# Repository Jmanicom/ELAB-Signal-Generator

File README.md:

# ELAB-Signal-Generator
A square wave generator with adjustable frequency, gain, and offset control. Designed as a part of UBC's ELAB PCB design course.

### **Skills used in this project**
***KiCad, Analog Circuit Design, Hand Soldering, Testing/Validation***

---

# Design
The design for this signal generator is not complex, this is because it's main purpose was to provide an opportunity to design 
and assemble a PCB from the start to finish of the production cycle. This included schematic capture, component/footprint library 
creation, component layout, laying traces, and laying polygon pours. In the second stage of the course, we received our boards and 
components and assembled them using hand soldering, and tested them using an oscilloscope to view our signals and test the various 
adjustments.

## Power Supply
The signal generator utilizes +/-5V rails to be able produce a maximum of a 10V peak-to-peak
signal. 15V  comes from a barrel jack connections from a wall adapter, which is then 
regulated using the **LM7805** to drop to it to +5V. This rail then feeds into the **MAX889** that
produces the complimentary -5V rail. Output capacitors are used to help with input noise, and output voltage ripple.

## Signal Amplifier
The square wave signal is generated by the **NE555**, that includes a frequency adjust potentiometer. This signal is then fed to 
the **AD8039** with two amplifier stages to control gain and offset respectively. Additional bypass capacitors are placed
on the op-amps power rails to help with further noise reduction and to help stabilize voltage. Finally, a 3.3V peak-limiter zener
diode is placed on the output which can be engaged with the use of a jumper. 

## PCB Design
With this being my first attempt at PCB design, there is room for improvement with my traces decisions component placement.
With this project, we were constrained on the size of board that we could use, additionally, I wanted to make a unique shape
for my board that tends to be a popular shape for small desings that need to be mounted.

The large 1206 capacitors were placed on the back side of the board as they are quite bulky and left very little room for other
components on the board. This board features 2-layers with ground pours on each layer, as well as stitching vias to help further
with noise.

# Assembly

# Testing

# Notes

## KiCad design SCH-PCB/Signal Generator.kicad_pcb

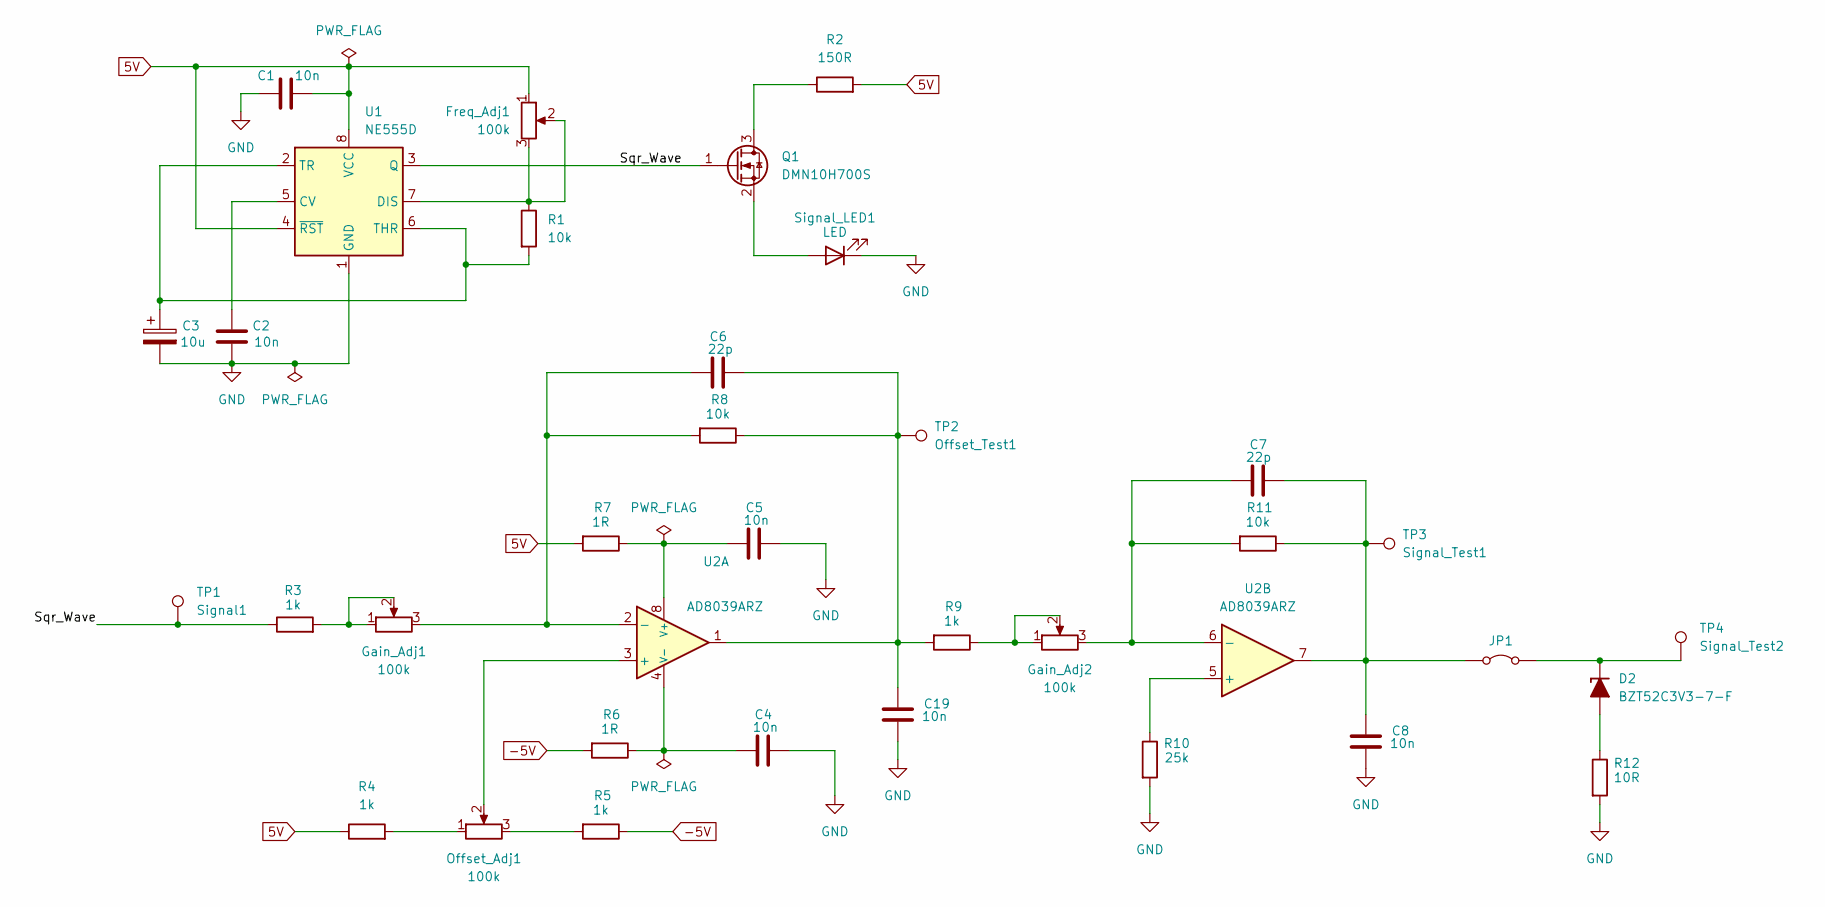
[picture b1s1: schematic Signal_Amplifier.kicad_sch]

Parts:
C1, C2, C4, C5, C8, C19: 10n; C_0805_2012Metric_Pad1.18x1.45mm_HandSolder
C3: 10u; CP_EIA-6032-28_Kemet-C_HandSolder
C6, C7: 22p; C_0805_2012Metric_Pad1.18x1.45mm_HandSolder
D2: BZT52C3V3-7-F; D_SOD-123
Freq_Adj1: 100k; Potentiometer_Bourns_3296W_Vertical
Gain_Adj1, Gain_Adj2: 100k; Potentiometer_Bourns_3296W_Vertical
JP1: Jumper_2_Bridged; PinHeader_1x02_P2.54mm_Vertical
Offset_Adj1: 100k; Potentiometer_Bourns_3296W_Vertical
Q1: DMN10H700S; SOT-23
R1, R8, R11: 10k; R_0805_2012Metric_Pad1.20x1.40mm_HandSolder
R2: 150R; R_0805_2012Metric_Pad1.20x1.40mm_HandSolder
R3, R4, R5, R9: 1k; R_0805_2012Metric_Pad1.20x1.40mm_HandSolder
R6, R7: 1R; R_0805_2012Metric_Pad1.20x1.40mm_HandSolder
R10: 25k; R_0805_2012Metric_Pad1.20x1.40mm_HandSolder
R12: 10R; R_0805_2012Metric_Pad1.20x1.40mm_HandSolder
Signal_LED1: LED; D_0805_2012Metric_Pad1.15x1.40mm_HandSolder
TP1: Signal1; TestPoint_Loop_D2.54mm_Drill1.5mm_Beaded
TP2: Offset_Test1; TestPoint_Loop_D2.54mm_Drill1.5mm_Beaded
TP3: Signal_Test1; TestPoint_Loop_D2.54mm_Drill1.5mm_Beaded
TP4: Signal_Test2; TestPoint_Loop_D2.54mm_Drill1.5mm_Beaded
U1: NE555D; SOIC-8_3.9x4.9mm_P1.27mm
U2: AD8039ARZ; SO-8_3.9x4.9mm_P1.27mm

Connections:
5V: C1.2, Freq_Adj1.1, R2.2, R4.1, R7.2, U1.4 (~RST), U1.8 (VCC); also elsewhere on the board
-5V: R5.1, R6.2; also elsewhere on the board
/Signal_Amplifier/Sqr_Wave: Q1.1 (G), R3.1, TP1.1 (1_1), U1.3 (Q)
GND: C1.1, C2.2, C3.2, C4.1, C5.1, C8.2, C19.2, R10.2, R12.2, Signal_LED1.1 (K), U1.1 (GND); also elsewhere on the board
unnamed: C6.1, C19.1, R8.1, R9.2, TP2.1 (1_1), U2.1
unnamed: D2.2 (A), R12.1
unnamed: D2.1 (K), JP1.2 (B), TP4.1 (1_1)
unnamed: Gain_Adj1.1, Gain_Adj1.2, R3.2
unnamed: Gain_Adj2.1, Gain_Adj2.2, R9.1
unnamed: C7.1, C8.1, JP1.1 (A), R11.1, TP3.1 (1_1), U2.7
unnamed: Offset_Adj1.1, R4.2
unnamed: Offset_Adj1.3, R5.2
unnamed: Q1.3 (D), R2.1
unnamed: Q1.2 (S), Signal_LED1.2 (A)
unnamed: C2.1, U1.5 (CV)
unnamed: Freq_Adj1.2, Freq_Adj1.3, R1.1, U1.7 (DIS)
unnamed: C3.1, R1.2, U1.2 (TR), U1.6 (THR)
unnamed: Offset_Adj1.2, U2.3 (+)
unnamed: C6.2, Gain_Adj1.3, R8.2, U2.2 (-)
unnamed: C5.2, R7.1, U2.8 (V+)
unnamed: C4.2, R6.1, U2.4 (V-)
unnamed: R10.1, U2.5 (+)
unnamed: C7.2, Gain_Adj2.3, R11.2, U2.6 (-)

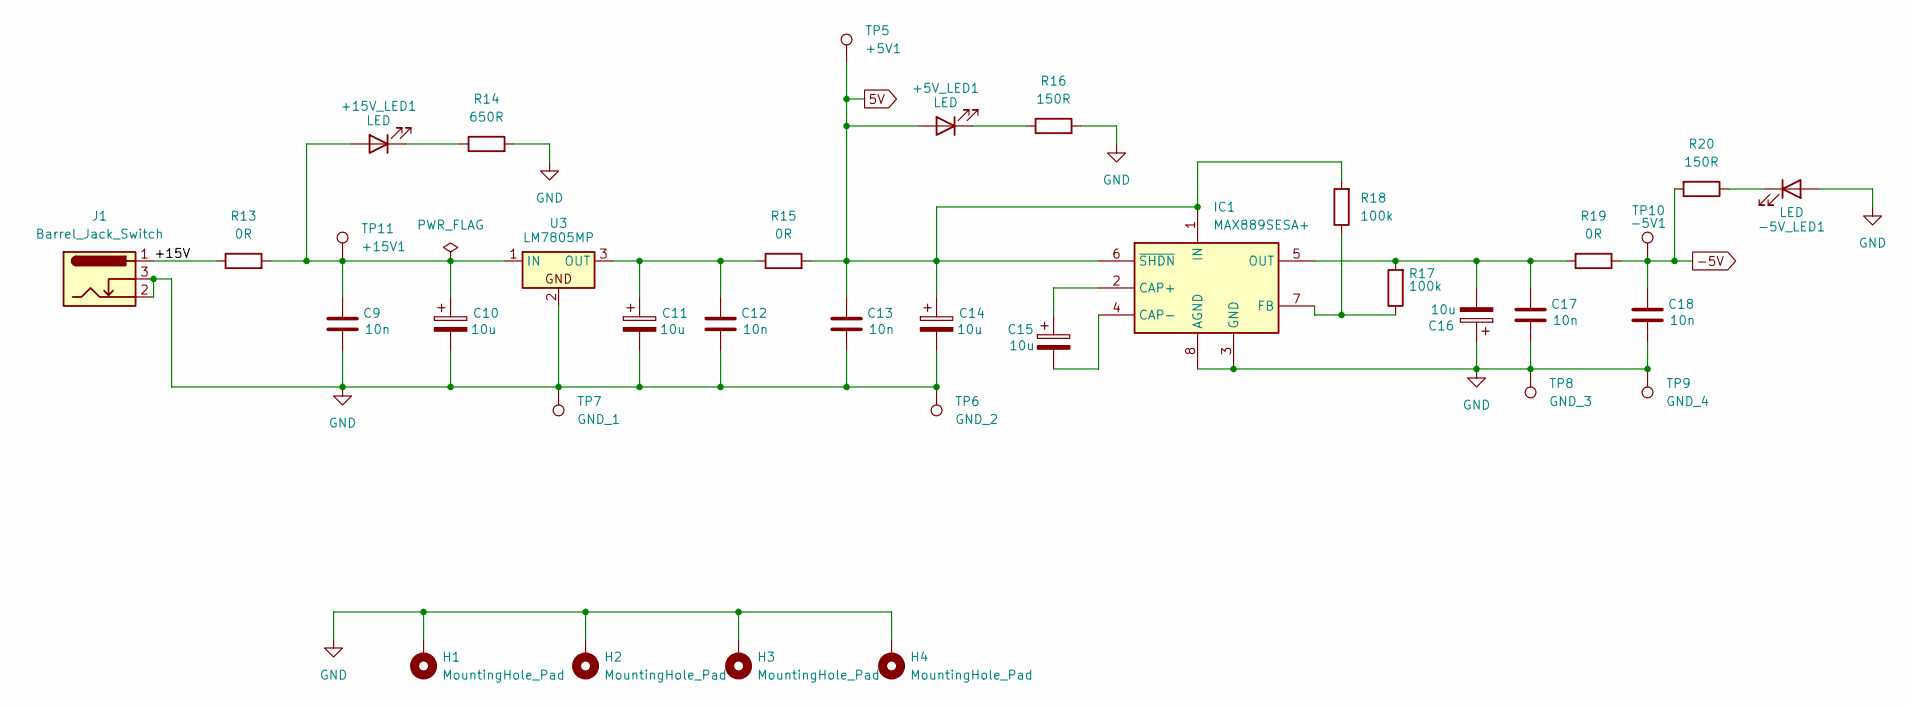
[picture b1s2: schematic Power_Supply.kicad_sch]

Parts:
+5V_LED1, +15V_LED1: LED; D_0805_2012Metric_Pad1.15x1.40mm_HandSolder
-5V_LED1: LED; D_0805_2012Metric_Pad1.15x1.40mm_HandSolder
C9, C12, C13, C17, C18: 10n; C_0805_2012Metric_Pad1.18x1.45mm_HandSolder
C10, C11, C14, C15, C16: 10u; CP_EIA-6032-28_Kemet-C_HandSolder
H1, H2, H3, H4: MountingHole_Pad; MountingHole_3.2mm_M3_DIN965_Pad
IC1: MAX889SESA+; SOIC-8_3.9x4.9mm_P1.27mm; Manufacturer_Part_Number MAX889SESA+; Mouser Part Number 700-MAX889SESA
J1: Barrel_Jack_Switch; CUI_PJ-002A
R13, R15, R19: 0R; R_0805_2012Metric_Pad1.20x1.40mm_HandSolder
R14: 650R; R_0805_2012Metric_Pad1.20x1.40mm_HandSolder
R16, R20: 150R; R_0805_2012Metric_Pad1.20x1.40mm_HandSolder
R17, R18: 100k; R_0805_2012Metric_Pad1.20x1.40mm_HandSolder
TP5: +5V1; TestPoint_Loop_D2.54mm_Drill1.5mm_Beaded
TP6: GND_2; TestPoint_Loop_D2.54mm_Drill1.5mm_Beaded
TP7: GND_1; TestPoint_Loop_D2.54mm_Drill1.5mm_Beaded
TP8: GND_3; TestPoint_Loop_D2.54mm_Drill1.5mm_Beaded
TP9: GND_4; TestPoint_Loop_D2.54mm_Drill1.5mm_Beaded
TP10: -5V1; TestPoint_Loop_D2.54mm_Drill1.5mm_Beaded
TP11: +15V1; TestPoint_Loop_D2.54mm_Drill1.5mm_Beaded
U3: LM7805MP; SOT-223-3_TabPin2

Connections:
5V: +5V_LED1.2 (A), C13.1, C14.1, IC1.1 (IN), IC1.6 (~SHDN), R15.2, R18.2, TP5.1 (1_1); also elsewhere on the board
-5V: C18.1, R19.1, R20.2, TP10.1 (1_1); also elsewhere on the board
/Power_Supply/+15V: J1.1, R13.1
GND: -5V_LED1.2 (A), C9.2, C10.2, C11.2, C12.2, C13.2, C14.2, C16.1, C17.2, C18.2, H1.1 (1_1), H2.1 (1_1), H3.1 (1_1), H4.1 (1_1), IC1.3 (GND), IC1.8 (AGND), J1.2, J1.3, R14.2, R16.2, TP6.1 (1_1), TP7.1 (1_1), TP8.1 (1_1), TP9.1 (1_1), U3.2; also elsewhere on the board
unnamed: +5V_LED1.1 (K), R16.1
unnamed: +15V_LED1.2 (A), C9.1, C10.1, R13.2, TP11.1 (1_1), U3.1 (IN)
unnamed: +15V_LED1.1 (K), R14.1
unnamed: -5V_LED1.1 (K), R20.1
unnamed: C15.1, IC1.2 (CAP+)
unnamed: C15.2, IC1.4 (CAP-)
unnamed: IC1.7 (FB), R17.1, R18.1
unnamed: C16.2, C17.1, IC1.5 (OUT), R17.2, R19.2
unnamed: C11.1, C12.1, R15.1, U3.3 (OUT)

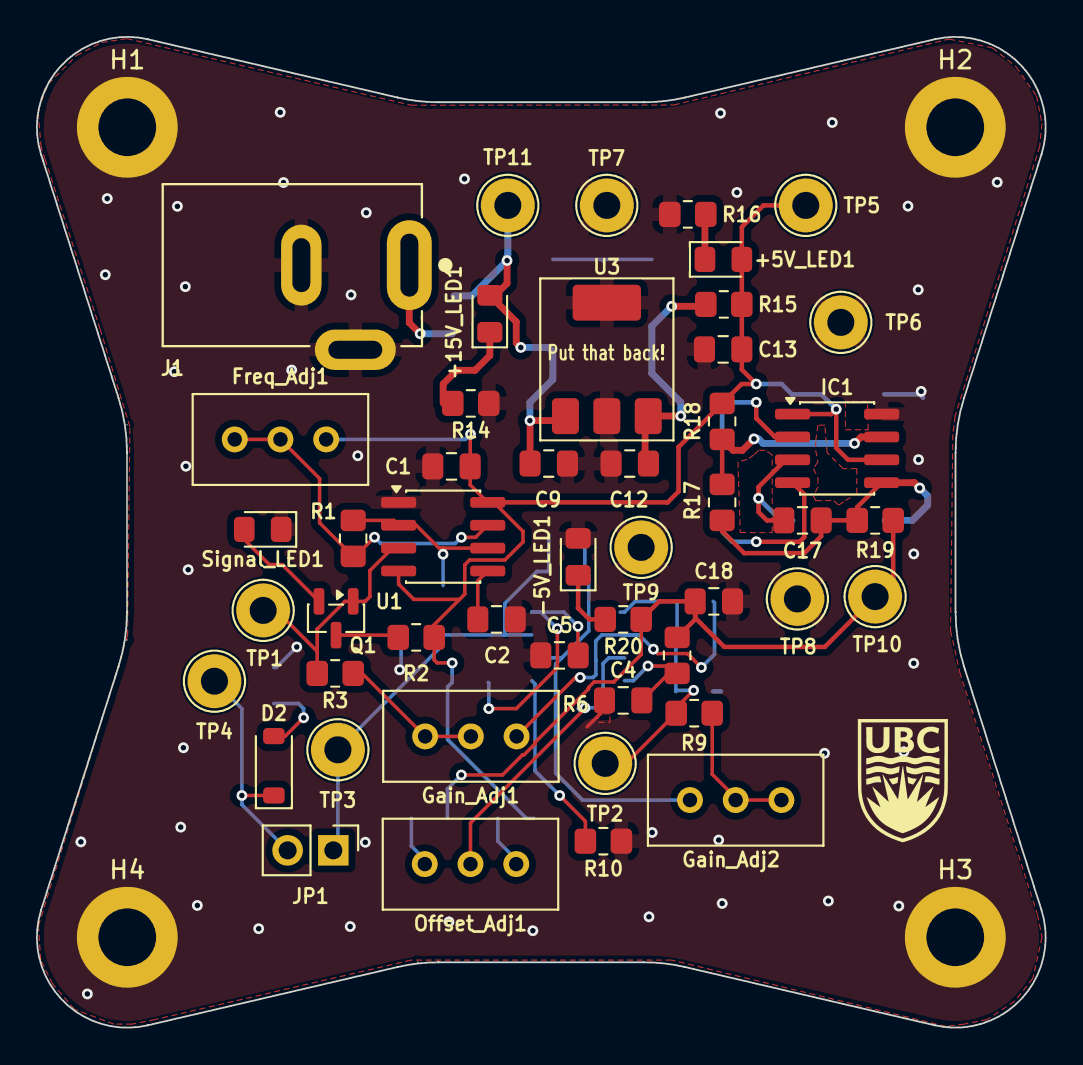
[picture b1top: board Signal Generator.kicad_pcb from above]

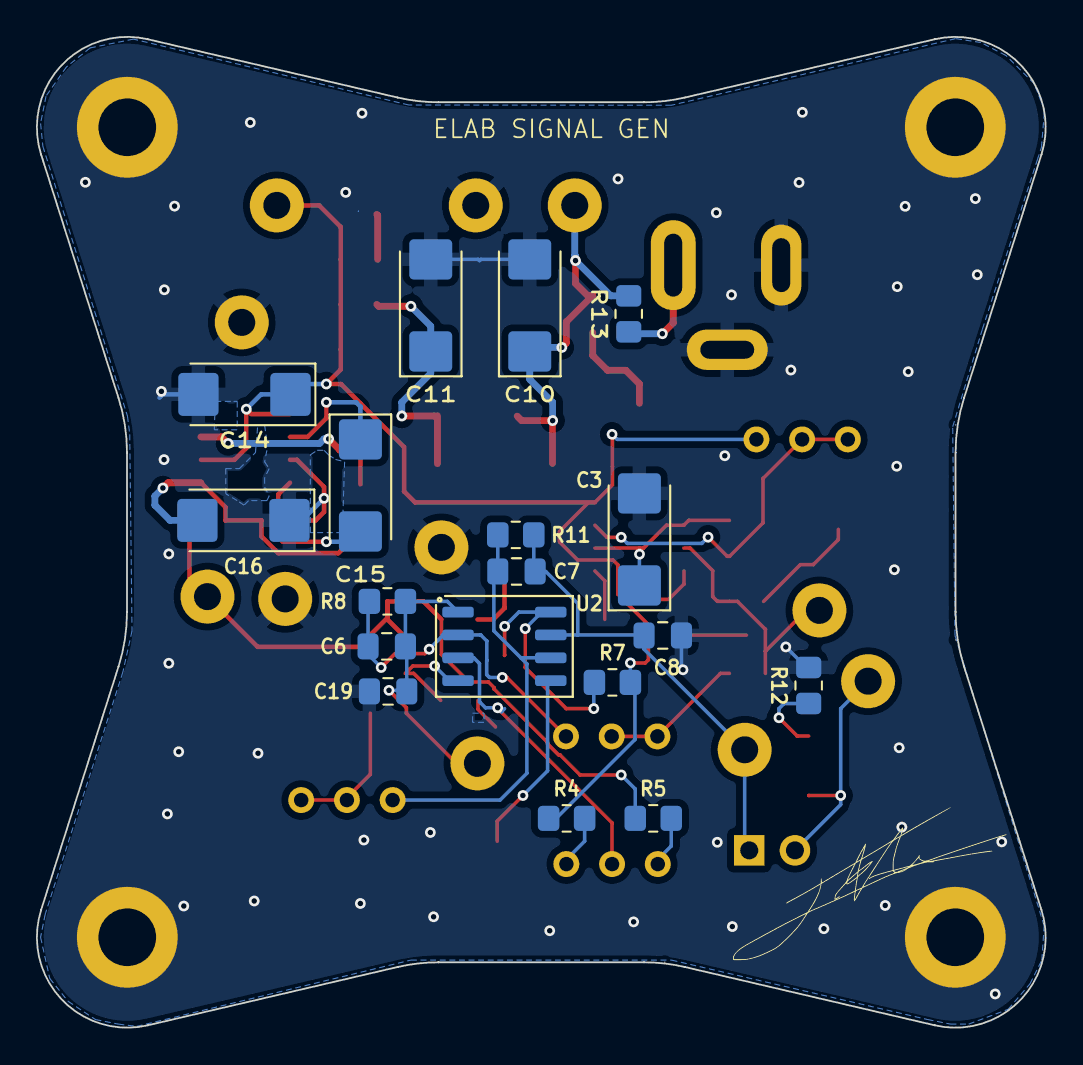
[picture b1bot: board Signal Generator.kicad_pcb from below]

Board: 2 copper layers, 56.0 x 55.0 mm, 70 parts (18 on the bottom side), 33 nets.
